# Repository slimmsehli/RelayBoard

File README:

🟢 4-Channel Relay Board with Opto-Isolation for Arduino/Raspberry Pi

This project is a modular, 4-channel relay control board designed for microcontrollers like **Arduino, Raspberry Pi, ESP32, etc.
The board features opto-isolation for electrical protection and safety, and is ideal for home automation, IoT, or industrial control applications.

---

## 📦 Features

- ✅ **4 independent relays** (SPDT type) – control AC/DC loads up to 250V AC / 30V DC
- ✅ **4 opto-isolated inputs** – control each relay with 3.3V or 5V logic
- ✅ **Load-side isolation** – added safety through PCB cutouts (drilled part under relay contacts)
- ✅ **Status indicator LEDs** – per-relay operation feedback
- ✅ Designed for **Arduino, Raspberry Pi, ESP8266, ESP32**, etc.
- ✅ Screw terminals for easy wiring of relays and power

---

## ⚙️ Technical Specs

| Feature              | Description                     |
|----------------------|---------------------------------|
| **Relay type**       | 5V SPDT                         |
| **Input voltage**    | 5V logic compatible             |
| **Isolation**        | Optical + PCB drilled spacing   |
| **Max switching**    | 10A 250V AC / 10A 30V DC        |
| **Board size**       | 65mmx70mm                       |
| **Control headers**  | 4-pin input control (IN1–IN4)   |
| **Load terminals**   | NO, COM, NC per relay           |

---

## 📌 Pinout

| Pin | Description           |
|-----|-----------------------|
| IN1 | Control for Relay 1   |
| IN2 | Control for Relay 2   |
| IN3 | Control for Relay 3   |
| IN4 | Control for Relay 4   |
| VCC | Input side power (5V) |
| GND | Ground                |

Each control input drives one relay via an optocoupler for full isolation.

---

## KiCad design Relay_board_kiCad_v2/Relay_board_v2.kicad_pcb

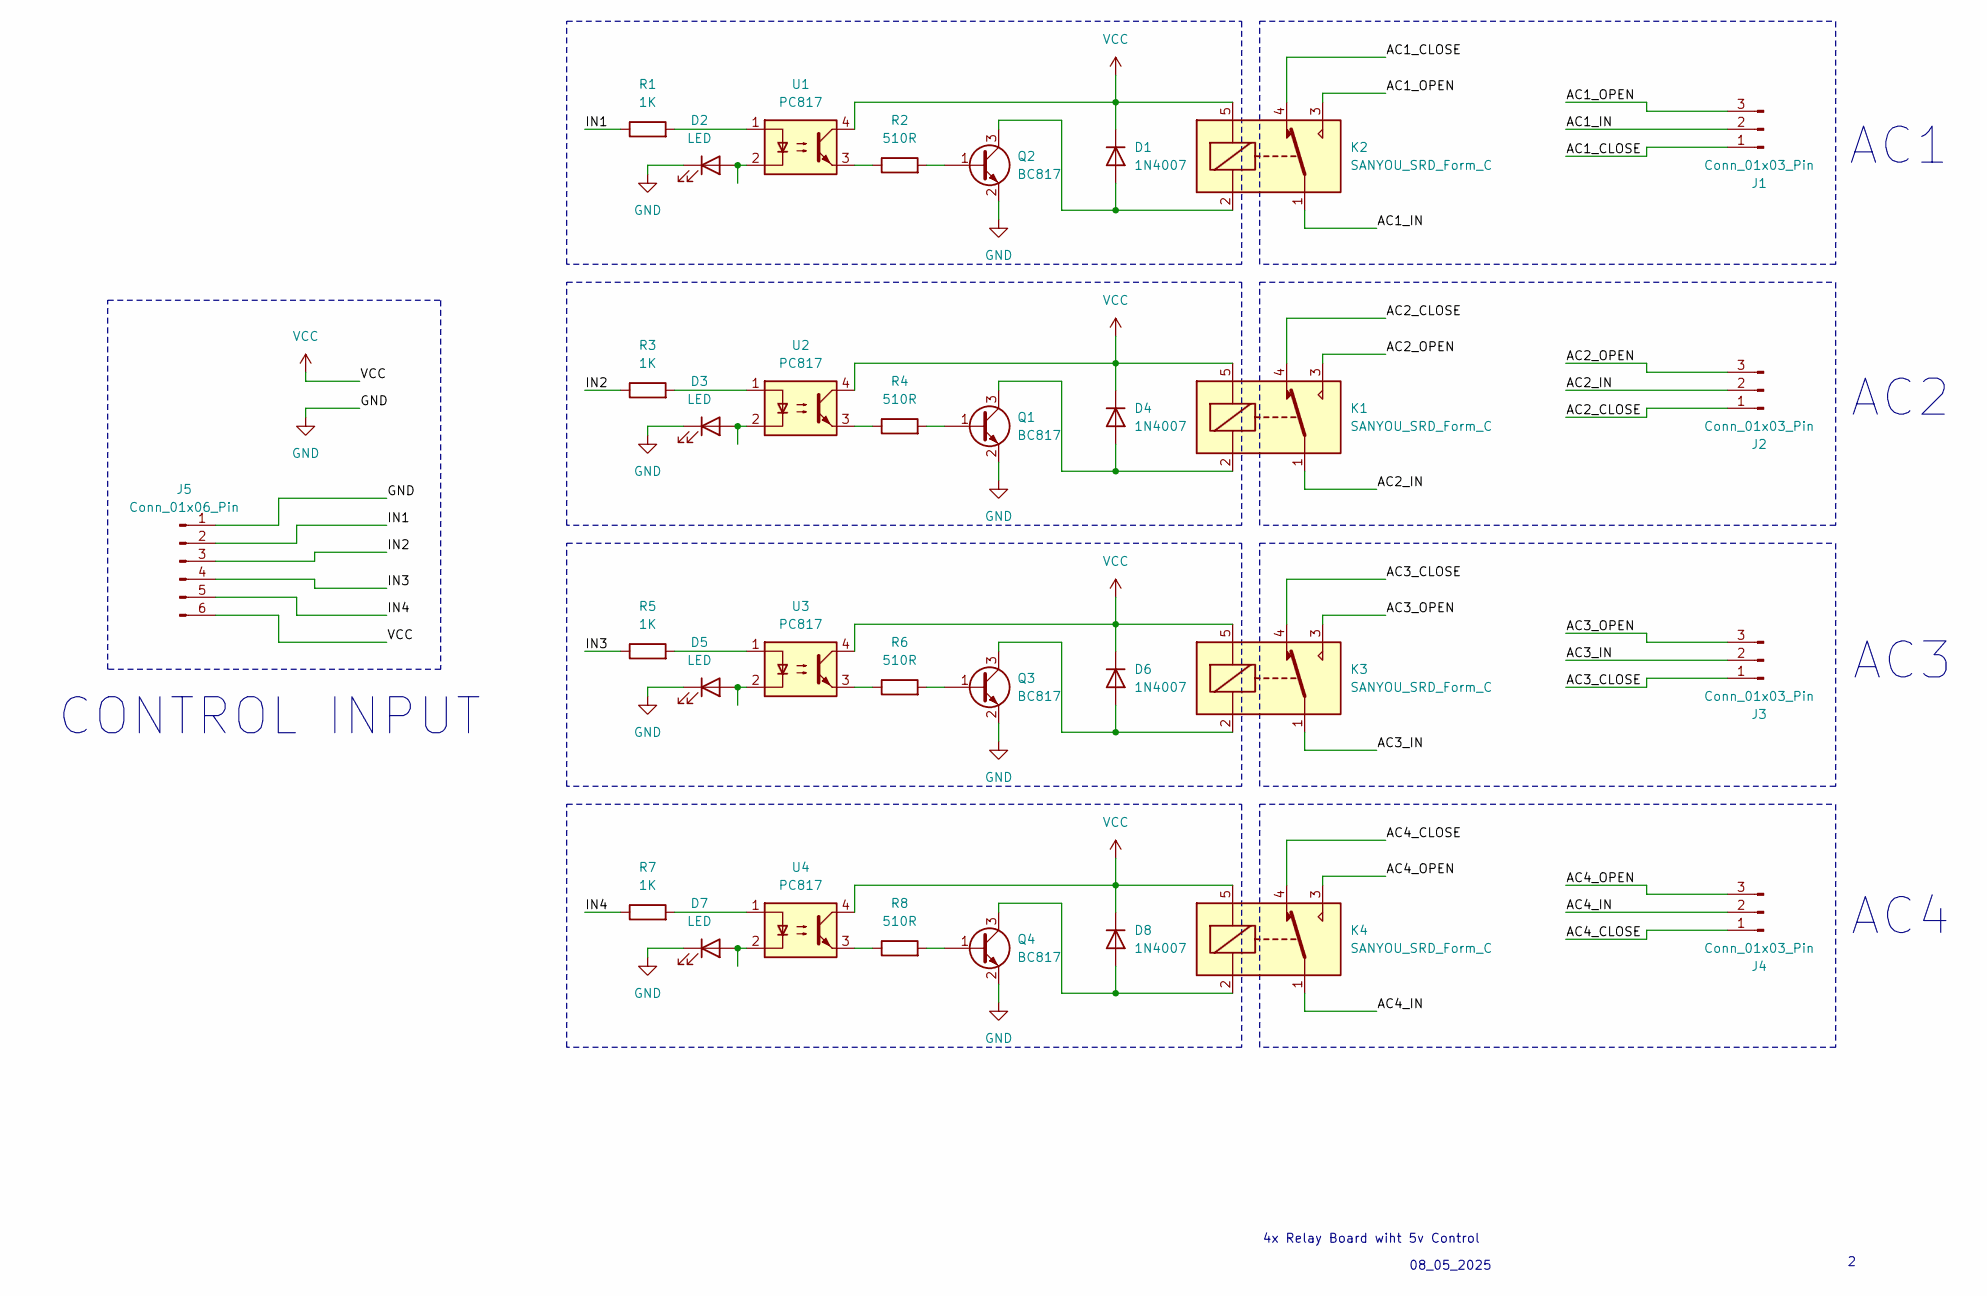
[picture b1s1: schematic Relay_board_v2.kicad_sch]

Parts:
D1, D4, D6, D8: 1N4007; D_DO-41_SOD81_P10.16mm_Horizontal
D2, D3, D5, D7: LED; LED_1206_3216Metric_Pad1.42x1.75mm_HandSolder
J1, J2, J3, J4: Conn_01x03_Pin; TerminalBlock_bornier-3_P5.08mm
J5: Conn_01x06_Pin; PinHeader_1x06_P2.54mm_Vertical
K1, K2, K3, K4: SANYOU_SRD_Form_C; Relay_SPDT_SANYOU_SRD_Series_Form_C
Q1, Q2, Q3, Q4: BC817; SOT-23
R1, R3, R5, R7: 1K; R_Axial_DIN0207_L6.3mm_D2.5mm_P10.16mm_Horizontal
R2, R4, R6, R8: 510R; R_Axial_DIN0207_L6.3mm_D2.5mm_P10.16mm_Horizontal
U1, U2, U3, U4: PC817; DIP-4_W7.62mm

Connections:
/AC1_CLOSE: J1.1, K2.4
/AC1_IN: J1.2, K2.1
/AC1_OPEN: J1.3, K2.3
/AC2_CLOSE: J2.1, K1.4
/AC2_IN: J2.2, K1.1
/AC2_OPEN: J2.3, K1.3
/AC3_CLOSE: J3.1, K3.4
/AC3_IN: J3.2, K3.1
/AC3_OPEN: J3.3, K3.3
/AC4_CLOSE: J4.1, K4.4
/AC4_IN: J4.2, K4.1
/AC4_OPEN: J4.3, K4.3
/IN1: J5.2, R1.1
/IN2: J5.3, R3.1
/IN3: J5.4, R5.1
/IN4: J5.5, R7.1
GND: D2.1 (K), D3.1 (K), D5.1 (K), D7.1 (K), J5.1, Q1.2 (E), Q2.2 (E), Q3.2 (E), Q4.2 (E)
unnamed: D1.2 (A), K2.2, Q2.3 (C)
unnamed: D2.2 (A), U1.2
unnamed: D3.2 (A), U2.2
unnamed: D4.2 (A), K1.2, Q1.3 (C)
unnamed: D5.2 (A), U3.2
unnamed: D6.2 (A), K3.2, Q3.3 (C)
unnamed: D7.2 (A), U4.2
unnamed: D8.2 (A), K4.2, Q4.3 (C)
unnamed: Q1.1 (B), R4.2
unnamed: Q2.1 (B), R2.2
unnamed: Q3.1 (B), R6.2
unnamed: Q4.1 (B), R8.2
unnamed: R1.2, U1.1
unnamed: R2.1, U1.3
unnamed: R3.2, U2.1
unnamed: R4.1, U2.3
unnamed: R5.2, U3.1
unnamed: R6.1, U3.3
unnamed: R7.2, U4.1
unnamed: R8.1, U4.3
VCC: D1.1 (K), D4.1 (K), D6.1 (K), D8.1 (K), J5.6, K1.5, K2.5, K3.5, K4.5, U1.4, U2.4, U3.4, U4.4

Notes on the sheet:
AC2
08_05_2025
AC3
4x Relay Board wiht 5v Control
CONTROL INPUT
AC1
AC4

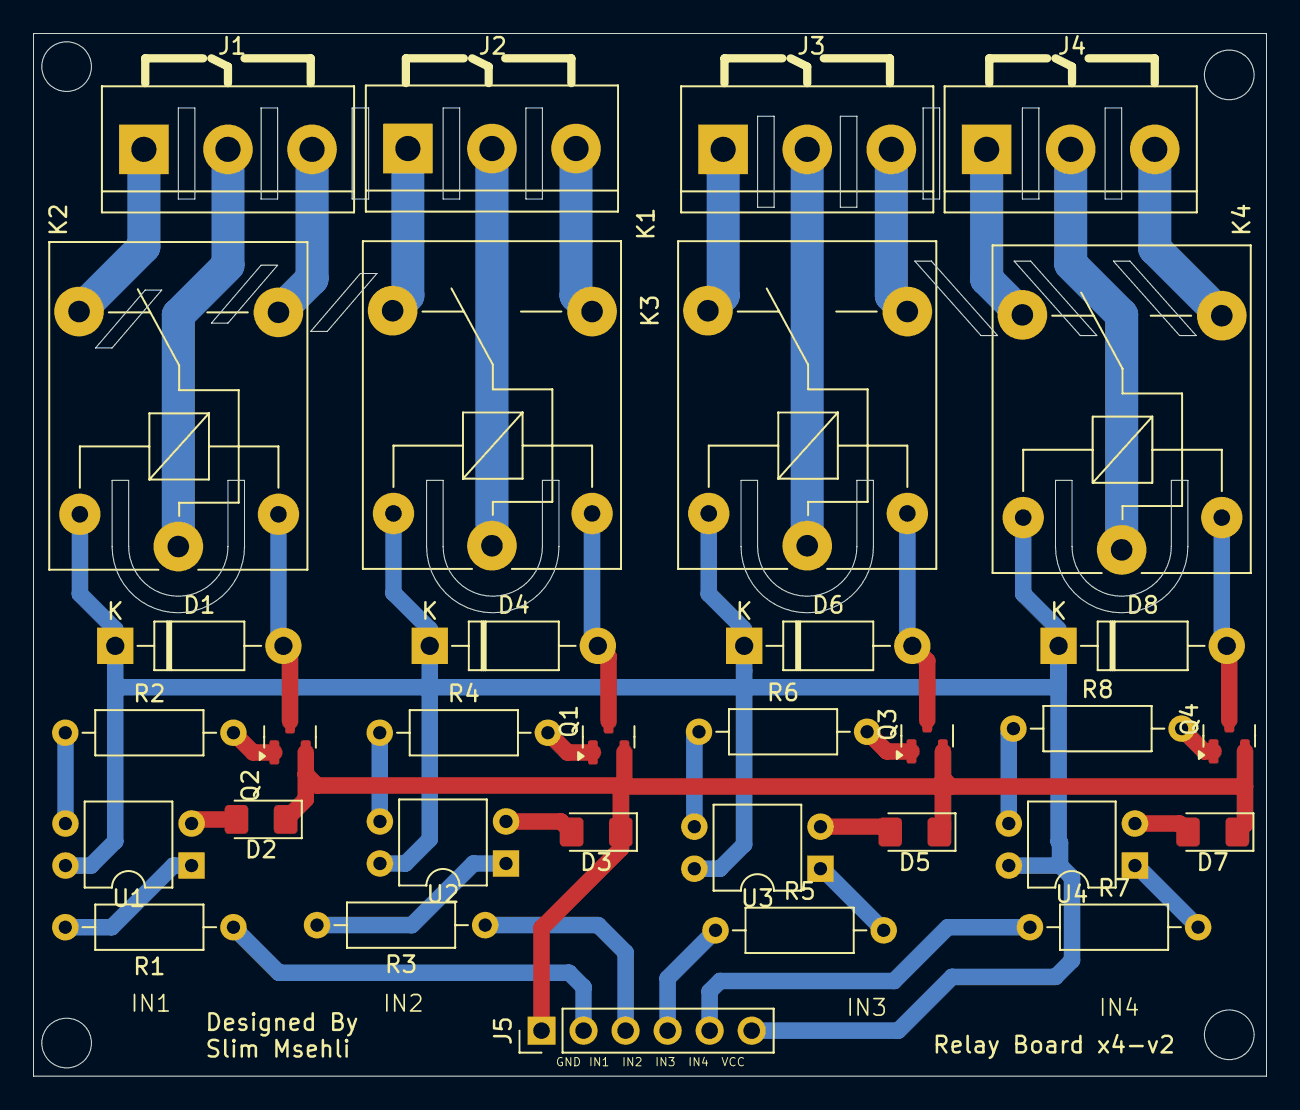
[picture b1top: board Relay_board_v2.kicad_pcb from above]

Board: 2 copper layers, 74.5 x 63.0 mm, 33 parts (0 on the bottom side), 38 nets.

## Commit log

2025-05-29 Add files via upload
    version 2 of the board with resistor footprint replacement and minor text change
2025-05-29 Add files via upload
    pinout replacement
